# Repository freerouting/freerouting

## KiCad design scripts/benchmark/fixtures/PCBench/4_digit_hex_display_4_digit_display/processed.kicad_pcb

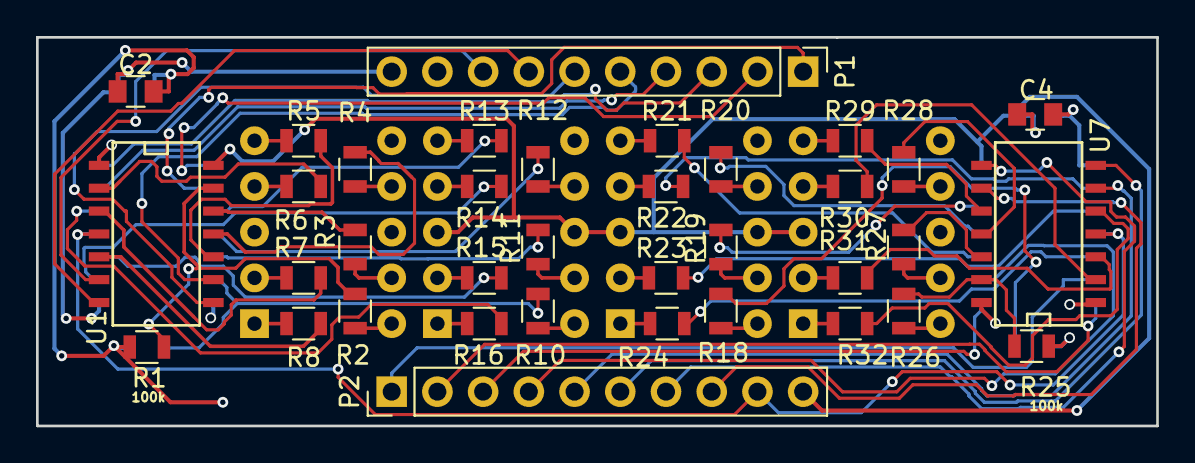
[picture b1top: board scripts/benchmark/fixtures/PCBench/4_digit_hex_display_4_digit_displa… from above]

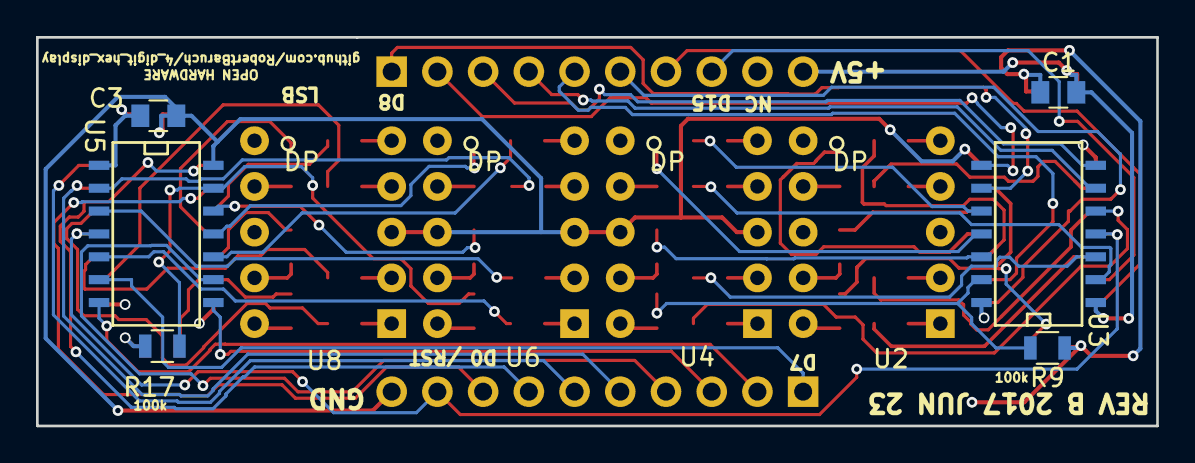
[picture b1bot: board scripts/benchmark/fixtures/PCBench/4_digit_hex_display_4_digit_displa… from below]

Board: 4 copper layers, 62.2 x 21.6 mm, 46 parts (10 on the bottom side), 75 nets.

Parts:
C1, C2, C3, C4: C; C_0805
P1, P2: CONN_01X10; Pin_Header_Straight_1x10_Pitch2.54mm
R1, R9, R17, R25: 100k; R_0805
R2, R3, R4, R5, R6, R7, R8, R10, R11, R12, R13, R14, R15, R16, R18, R19, R20, R21, R22, R23, R24, R26, R27, R28, R29, R30, R31, R32: 3k3; R_0805
U1, U3, U5, U7: ATTINY84A-SS; SOIC-14_N
U2, U4, U6, U8: TDSR1060; TDSR10

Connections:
+5V: C1.1, C2.1, C3.1, C4.1, P1.10, U1.1, U3.1, U5.1, U7.1
//RST: P2.9, U1.4, U3.4, U5.4, U7.4
/D0: P2.8, U7.9
/D1: P2.7, U7.8
/D2: P2.6, U7.7
/D3: P2.5, U7.6
/D4: P2.4, U5.9
/D5: P2.3, U5.8
/D6: P2.2, U5.7
/D7: P2.1, U5.6
/D8: P1.1, U3.9
/D9: P1.2, U3.8
/D10: P1.3, U3.7
/D11: P1.4, U3.6
/D12: P1.5, U1.9
/D13: P1.6, U1.8
/D14: P1.7, U1.7
/D15: P1.8, U1.6
GNDREF: C1.2, C2.2, C3.2, C4.2, P2.10, R1.1, R9.1, R17.1, R25.1, U1.14, U2.3, U2.8, U3.14, U4.3, U4.8, U5.14, U6.3, U6.8, U7.14, U8.3, U8.8
unnamed: R1.2, R2.2, U1.13
unnamed: R2.1, U2.10
unnamed: R3.1, U2.9
unnamed: R3.2, U1.12
unnamed: R4.1, U2.7
unnamed: R4.2, U1.11
unnamed: R5.1, U2.5
unnamed: R5.2, U1.10
unnamed: R6.1, U2.4
unnamed: R6.2, U1.2
unnamed: R7.1, U2.2
unnamed: R7.2, U1.3
unnamed: R8.1, U2.1
unnamed: R8.2, U1.5
unnamed: R10.1, U4.10
unnamed: R9.2, R10.2, U3.13
unnamed: R11.1, U4.9
unnamed: R11.2, U3.12
unnamed: R12.1, U4.7
unnamed: R12.2, U3.11
unnamed: R13.1, U4.5
unnamed: R13.2, U3.10
unnamed: R14.1, U4.4
unnamed: R14.2, U3.2
unnamed: R15.1, U4.2
unnamed: R15.2, U3.3
unnamed: R16.1, U4.1
unnamed: R16.2, U3.5
unnamed: R17.2, R18.2, U5.13
unnamed: R18.1, U6.10
unnamed: R19.1, U6.9
unnamed: R19.2, U5.12
unnamed: R20.1, U6.7
unnamed: R20.2, U5.11
unnamed: R21.1, U6.5
unnamed: R21.2, U5.10
unnamed: R22.1, U6.4
unnamed: R22.2, U5.2
unnamed: R23.1, U6.2
unnamed: R23.2, U5.3
unnamed: R24.1, U6.1
unnamed: R24.2, U5.5
unnamed: R25.2, R26.2, U7.13
unnamed: R26.1, U8.10
unnamed: R27.1, U8.9
unnamed: R27.2, U7.12
unnamed: R28.1, U8.7
unnamed: R28.2, U7.11
unnamed: R29.1, U8.5
unnamed: R29.2, U7.10
unnamed: R30.1, U8.4
unnamed: R30.2, U7.2
unnamed: R31.1, U8.2
unnamed: R31.2, U7.3
unnamed: R32.1, U8.1
unnamed: R32.2, U7.5

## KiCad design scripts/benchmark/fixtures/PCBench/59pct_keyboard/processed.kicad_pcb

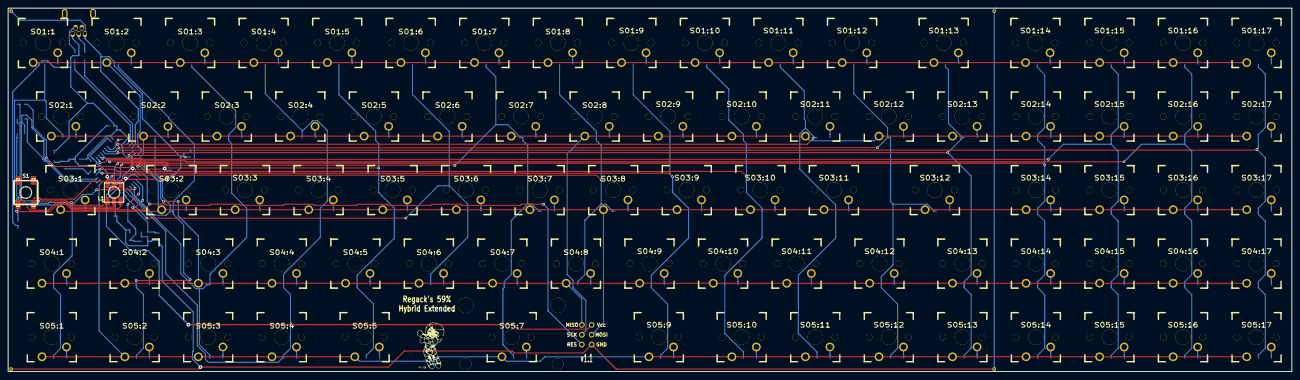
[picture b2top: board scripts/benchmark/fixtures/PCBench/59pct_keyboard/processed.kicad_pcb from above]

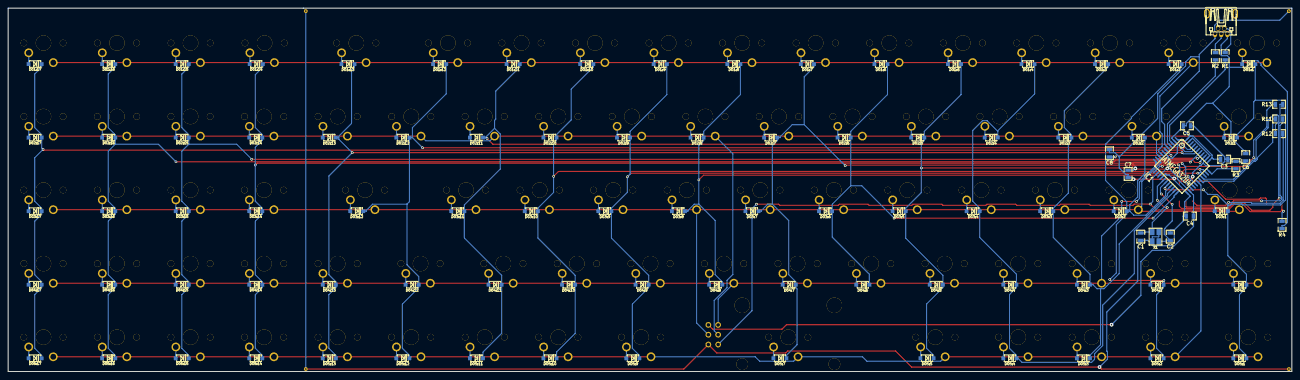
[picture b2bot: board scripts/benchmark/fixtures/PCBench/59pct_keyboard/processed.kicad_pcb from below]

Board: 2 copper layers, 332.5 x 94.1 mm, 195 parts (104 on the bottom side), 121 nets.

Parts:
C1, C2: 22pF; SM0805
C3, C4, C5, C6: 0.1uF; SM0805
C7, C8: 1uF; SM0805
D01:1, D01:2, D01:3, D01:4, D01:5, D01:6, D01:7, D01:8, D01:9, D01:10, D01:11, D01:12, D01:13, D01:14, D01:15, D01:16, D01:17, D02:1, D02:2, D02:3, D02:4, D02:5, D02:6, D02:7, D02:8, D02:9, D02:10, D02:11, D02:12, D02:13, D02:14, D02:15, D02:16, D02:17, D03:1, D03:2, D03:3, D03:4, D03:5, D03:6, D03:7, D03:8, D03:9, D03:10, D03:11, D03:12, D03:14, D03:15, D03:16, D03:17, D04:1, D04:2, D04:3, D04:4, D04:5, D04:6, D04:7, D04:8, D04:9, D04:10, D04:11, D04:12, D04:13, D04:14, D04:15, D04:16, D04:17, D05:1, D05:2, D05:3, D05:4, D05:5, D05:7, D05:9, D05:10, D05:11, D05:12, D05:13, D05:14, D05:15, D05:16, D05:17: 1N4148; SOD-123(A-C)
G4: Graphic; Silkscreen_Regack_100x150
IC1: ATMEGA32U4; TQFP44
J1: USB MINI-B; USB_MINI-B_MOLEX_54819-0519
L1: RGB_SMD_LED; RGBLED5050
P1, P2, P3, P4: GND; Pad_Gnd
P5: MISO; Pad
P6: Vcc; Pad
P7: SCK; Pad
P8: MOSI; Pad
P9: RES; Pad
P10: GND; Pad
R1, R2: 22Ω; SM0805
R3, R4: 10kΩ; SM0805
R11, R13: RESISTOR; SM0805
R12: 120; SM0805
S1: ADTSMW69NVTR; ADTSJW65RV
S01:1, S01:2, S01:3, S01:4, S01:5, S01:6, S01:7, S01:8, S01:9, S01:10, S01:11, S01:12, S01:14, S01:15, S01:16, S01:17, S02:2, S02:3, S02:4, S02:5, S02:6, S02:7, S02:8, S02:9, S02:10, S02:11, S02:12, S02:13, S02:14, S02:15, S02:16, S02:17, S03:2, S03:3, S03:4, S03:5, S03:6, S03:7, S03:8, S03:9, S03:10, S03:11, S03:14, S03:15, S03:16, S03:17, S04:2, S04:3, S04:4, S04:5, S04:6, S04:7, S04:8, S04:9, S04:10, S04:11, S04:13, S04:14, S04:15, S04:16, S04:17, S05:2, S05:3, S05:4, S05:10, S05:11, S05:12, S05:13, S05:14, S05:15, S05:16, S05:17: MX1A; CHERRY_PCB_100H_Plated
S01:13, S02:1: MX1A; CHERRY_PCB_150H_Visible
S03:1, S03:12: MX1A; CHERRY_PCB_175H_Visible
S04:1, S04:12, S05:1, S05:5, S05:9: MX1A; CHERRY_PCB_125H_Visible
S05:7: MX1A; CHERRY_PCB_275H_Visible
X1: 7M-16.000MAAJ-T

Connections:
/Matrix/col1: D01:1.C, D02:1.C, D03:1.C, D04:1.C, D05:1.C, IC1.18
/Matrix/col2: D01:2.C, D02:2.C, D03:2.C, D04:2.C, D05:2.C, IC1.19
/Matrix/col3: D01:3.C, D02:3.C, D03:3.C, D04:3.C, D05:3.C, IC1.20
/Matrix/col4: D01:4.C, D02:4.C, D03:4.C, D04:4.C, D05:4.C, IC1.21
/Matrix/col5: D01:5.C, D02:5.C, D03:5.C, D04:5.C, D05:5.C, IC1.25
/Matrix/col6: D01:6.C, D02:6.C, D03:6.C, D04:6.C, IC1.22
/Matrix/col7: D01:7.C, D02:7.C, D03:7.C, D04:7.C, D05:7.C, IC1.26
/Matrix/col8: D01:8.C, D02:8.C, D03:8.C, D04:8.C, IC1.27
/Matrix/col9: D01:9.C, D02:9.C, D03:9.C, D04:9.C, D05:9.C, IC1.31
/Matrix/col10: D01:10.C, D02:10.C, D03:10.C, D04:10.C, D05:10.C, IC1.32
/Matrix/col11: D01:11.C, D02:11.C, D03:11.C, D04:11.C, D05:11.C, IC1.41
/Matrix/col12: D01:12.C, D02:12.C, D03:12.C, D04:12.C, D05:12.C, IC1.40
/Matrix/col13: D01:13.C, D02:13.C, D04:13.C, D05:13.C, IC1.39
/Matrix/col14: D01:14.C, D02:14.C, D03:14.C, D04:14.C, D05:14.C, IC1.38
/Matrix/col15: D01:15.C, D02:15.C, D03:15.C, D04:15.C, D05:15.C, IC1.37
/Matrix/col16: D01:16.C, D02:16.C, D03:16.C, D04:16.C, D05:16.C, IC1.36
/Matrix/col17: D01:17.C, D02:17.C, D03:17.C, D04:17.C, D05:17.C, IC1.1
/Matrix/row1: IC1.8, S01:1.1, S01:2.1, S01:3.1, S01:4.1, S01:5.1, S01:6.1, S01:7.1, S01:8.1, S01:9.1, S01:10.1, S01:11.1, S01:12.1, S01:13.1, S01:14.1, S01:15.1, S01:16.1, S01:17.1
/Matrix/row2: IC1.9, P7.1, S02:1.1, S02:2.1, S02:3.1, S02:4.1, S02:5.1, S02:6.1, S02:7.1, S02:8.1, S02:9.1, S02:10.1, S02:11.1, S02:12.1, S02:13.1, S02:14.1, S02:15.1, S02:16.1, S02:17.1
/Matrix/row3: IC1.10, P8.1, S03:1.1, S03:2.1, S03:3.1, S03:4.1, S03:5.1, S03:6.1, S03:7.1, S03:8.1, S03:9.1, S03:10.1, S03:11.1, S03:12.1, S03:14.1, S03:15.1, S03:16.1, S03:17.1
/Matrix/row4: IC1.11, P5.1, S04:1.1, S04:2.1, S04:3.1, S04:4.1, S04:5.1, S04:6.1, S04:7.1, S04:8.1, S04:9.1, S04:10.1, S04:11.1, S04:12.1, S04:13.1, S04:14.1, S04:15.1, S04:16.1, S04:17.1
/Matrix/row5: IC1.28, S05:1.1, S05:2.1, S05:3.1, S05:4.1, S05:5.1, S05:7.1, S05:9.1, S05:10.1, S05:11.1, S05:12.1, S05:13.1, S05:14.1, S05:15.1, S05:16.1, S05:17.1
/PWM1: IC1.29, R11.2
/PWM2: IC1.30, R12.2
/PWM3: IC1.12, R13.2
/~RES~: IC1.13, P9.1, R4.2, S1.4
GND: C1.2, C2.2, C3.2, C4.2, C5.2, C6.2, C7.2, C8.2, IC1.5, IC1.15, IC1.23, IC1.35, IC1.43, J1.5, L1.4, L1.5, L1.6, P1.1, P2.1, P3.1, P4.1, P10.1, R3.2, S1.2, X1.2, X1.4
unnamed: J1.2, R1.2
unnamed: J1.3, R2.2
unnamed: IC1.4, R2.1
unnamed: IC1.3, R1.1
unnamed: IC1.33, R3.1
unnamed: C8.1, IC1.6
unnamed: L1.1, R12.1
unnamed: C1.1, IC1.16, X1.1
unnamed: C2.1, IC1.17, X1.3
unnamed: L1.3, R13.1
unnamed: L1.2, R11.1
unnamed: D04:1.A, S04:1.2
unnamed: D04:13.A, S04:13.2
unnamed: D05:11.A, S05:11.2
unnamed: D05:12.A, S05:12.2
unnamed: D05:13.A, S05:13.2
unnamed: D05:7.A, S05:7.2
unnamed: D03:1.A, S03:1.2
unnamed: D05:4.A, S05:4.2
unnamed: D05:1.A, S05:1.2
unnamed: D05:2.A, S05:2.2
unnamed: D05:3.A, S05:3.2
unnamed: D05:5.A, S05:5.2
unnamed: D05:9.A, S05:9.2
unnamed: D05:10.A, S05:10.2
unnamed: D03:12.A, S03:12.2
unnamed: D04:9.A, S04:9.2
unnamed: D04:10.A, S04:10.2
unnamed: D04:11.A, S04:11.2
unnamed: D04:12.A, S04:12.2
unnamed: D03:11.A, S03:11.2
unnamed: D02:13.A, S02:13.2
unnamed: D02:12.A, S02:12.2
unnamed: D02:5.A, S02:5.2
unnamed: D03:9.A, S03:9.2
unnamed: D02:9.A, S02:9.2
unnamed: D01:10.A, S01:10.2
unnamed: D01:13.A, S01:13.2
unnamed: D02:10.A, S02:10.2
unnamed: D01:11.A, S01:11.2
unnamed: D02:11.A, S02:11.2
unnamed: D03:10.A, S03:10.2
unnamed: D04:8.A, S04:8.2
unnamed: D01:12.A, S01:12.2
unnamed: D04:5.A, S04:5.2
unnamed: D04:7.A, S04:7.2
unnamed: D05:14.A, S05:14.2
unnamed: D05:15.A, S05:15.2
unnamed: D05:16.A, S05:16.2
unnamed: D05:17.A, S05:17.2
unnamed: D04:15.A, S04:15.2
unnamed: D04:16.A, S04:16.2
unnamed: D04:17.A, S04:17.2
unnamed: D01:16.A, S01:16.2
unnamed: D01:17.A, S01:17.2
unnamed: D02:14.A, S02:14.2
unnamed: D02:15.A, S02:15.2
unnamed: D01:14.A, S01:14.2
unnamed: D01:15.A, S01:15.2
unnamed: D03:15.A, S03:15.2
unnamed: D03:16.A, S03:16.2
unnamed: D03:17.A, S03:17.2
unnamed: D04:14.A, S04:14.2
unnamed: D02:16.A, S02:16.2
unnamed: D02:17.A, S02:17.2
unnamed: D03:14.A, S03:14.2
unnamed: D01:7.A, S01:7.2
unnamed: D01:9.A, S01:9.2
unnamed: D04:4.A, S04:4.2
unnamed: D02:2.A, S02:2.2
unnamed: D02:3.A, S02:3.2
unnamed: D02:4.A, S02:4.2
unnamed: D02:6.A, S02:6.2
unnamed: D02:7.A, S02:7.2
unnamed: D02:1.A, S02:1.2
unnamed: D02:8.A, S02:8.2
unnamed: D01:6.A, S01:6.2
unnamed: D01:1.A, S01:1.2
unnamed: D01:2.A, S01:2.2
unnamed: D01:3.A, S01:3.2
unnamed: D01:4.A, S01:4.2
unnamed: D01:5.A, S01:5.2
unnamed: D01:8.A, S01:8.2
unnamed: D04:2.A, S04:2.2
unnamed: D04:3.A, S04:3.2
unnamed: D04:6.A, S04:6.2
unnamed: D03:2.A, S03:2.2
unnamed: D03:3.A, S03:3.2
unnamed: D03:4.A, S03:4.2
unnamed: D03:5.A, S03:5.2
unnamed: D03:6.A, S03:6.2
unnamed: D03:7.A, S03:7.2
unnamed: D03:8.A, S03:8.2
VCC: C3.1, C4.1, C5.1, C6.1, C7.1, IC1.2, IC1.7, IC1.14, IC1.24, IC1.34, IC1.44, J1.1, P6.1, R4.1

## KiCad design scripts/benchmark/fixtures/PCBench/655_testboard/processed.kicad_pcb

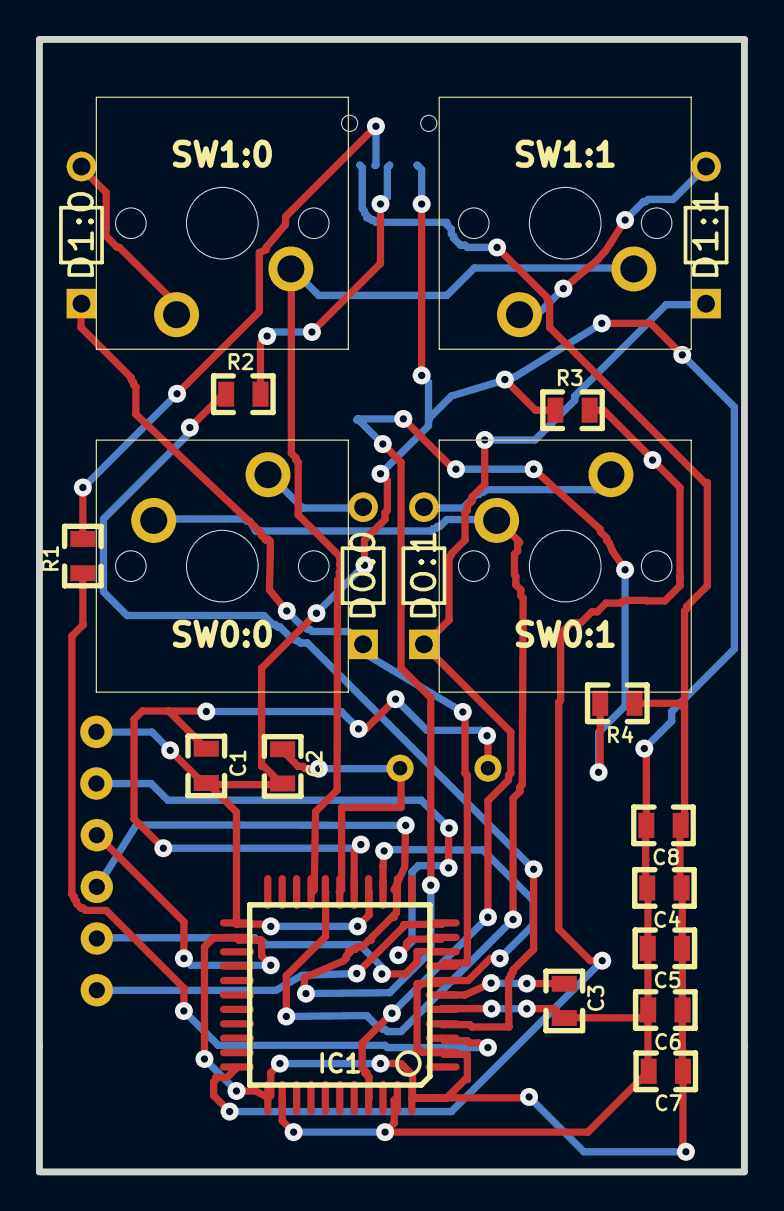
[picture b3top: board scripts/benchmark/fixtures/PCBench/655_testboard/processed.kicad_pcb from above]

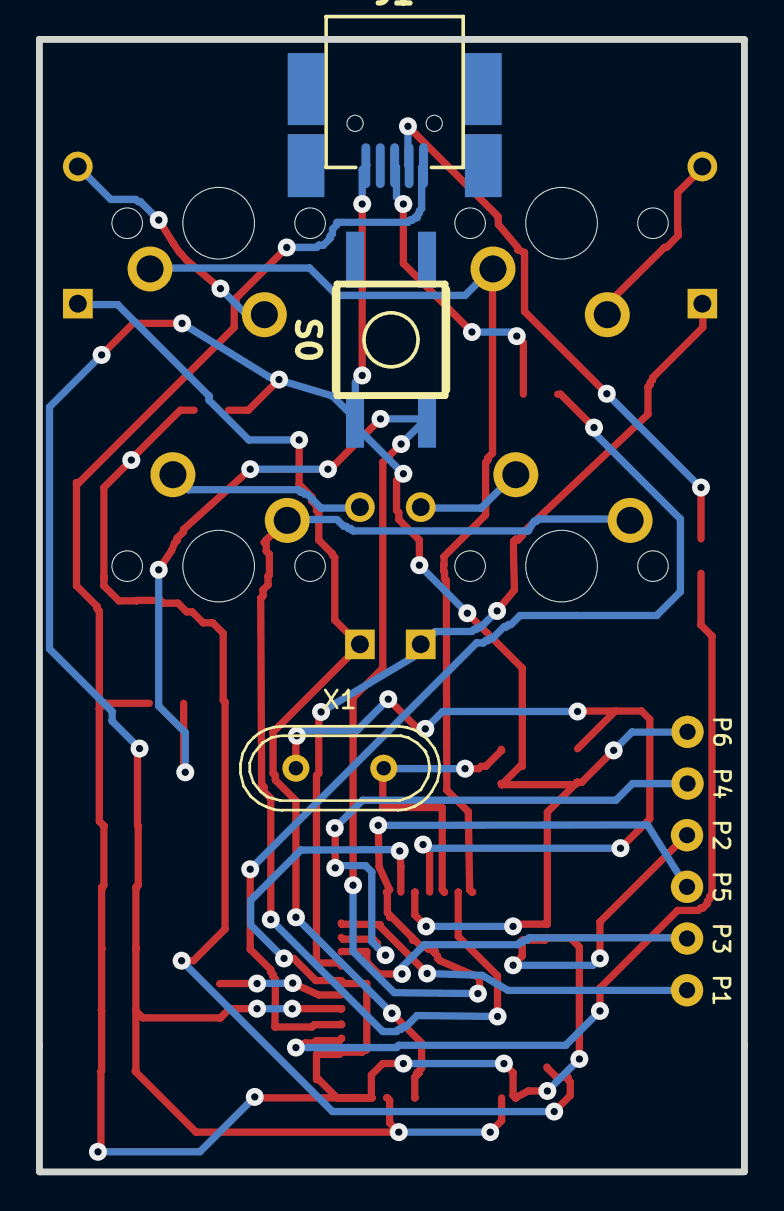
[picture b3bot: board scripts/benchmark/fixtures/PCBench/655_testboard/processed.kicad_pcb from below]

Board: 2 copper layers, 39.2 x 62.9 mm, 30 parts (9 on the bottom side), 22 nets.

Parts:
C1, C2: 22p; 0805C
C3, C8: 1u; 0805C
C4, C5, C6, C7: 100n; 0805C
D0:0, D0:1, D1:0, D1:1: D; DIODE
IC1: ATMEGA32U4; TQFP44
J1: USBMINI_B05; 67503
P1, P2, P3, P4, P5, P6: CONN_1; pad
R1, R2: 22; 0805R
R3, R4: 10k; 0805R
S0: DTSM-6; KSEM31GLFS
SW0:0: F0; MX1A
SW0:1: CTRL; MX1A
SW1:0: F1; MX1A
SW1:1: SHIFT; MX1A
X1: CRYSTAL; Crystal_HC49-U_Vertical

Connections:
/COL0: D0:0.2, D1:0.2, IC1.8
/COL1: D0:1.2, D1:1.2, IC1.41
/MISO: IC1.11, P1.1
/MOSI: IC1.10, P4.1
/RES: IC1.13, P5.1, R4.2, S0.3
/ROW0: IC1.18, SW0:0.1, SW0:1.1
/ROW1: IC1.19, SW1:0.1, SW1:1.1
/SCK: IC1.9, P3.1
GND: C1.2, C2.2, C3.2, C4.2, C5.2, C6.2, C7.2, C8.2, IC1.5, IC1.15, IC1.23, IC1.35, IC1.43, J1.5, P6.1, R3.1, S0.1
unnamed: C1.1, IC1.16, X1.1
unnamed: C2.1, IC1.17, X1.2
unnamed: C3.1, IC1.6
unnamed: D0:0.1, SW0:0.2
unnamed: D0:1.1, SW0:1.2
unnamed: D1:0.1, SW1:0.2
unnamed: D1:1.1, SW1:1.2
unnamed: IC1.3, R1.1
unnamed: IC1.4, R2.1
unnamed: IC1.33, R3.2
unnamed: J1.2, R1.2
unnamed: J1.3, R2.2
VCC: C4.1, C5.1, C6.1, C7.1, C8.1, IC1.2, IC1.7, IC1.14, IC1.24, IC1.34, IC1.44, J1.1, P2.1, R4.1
